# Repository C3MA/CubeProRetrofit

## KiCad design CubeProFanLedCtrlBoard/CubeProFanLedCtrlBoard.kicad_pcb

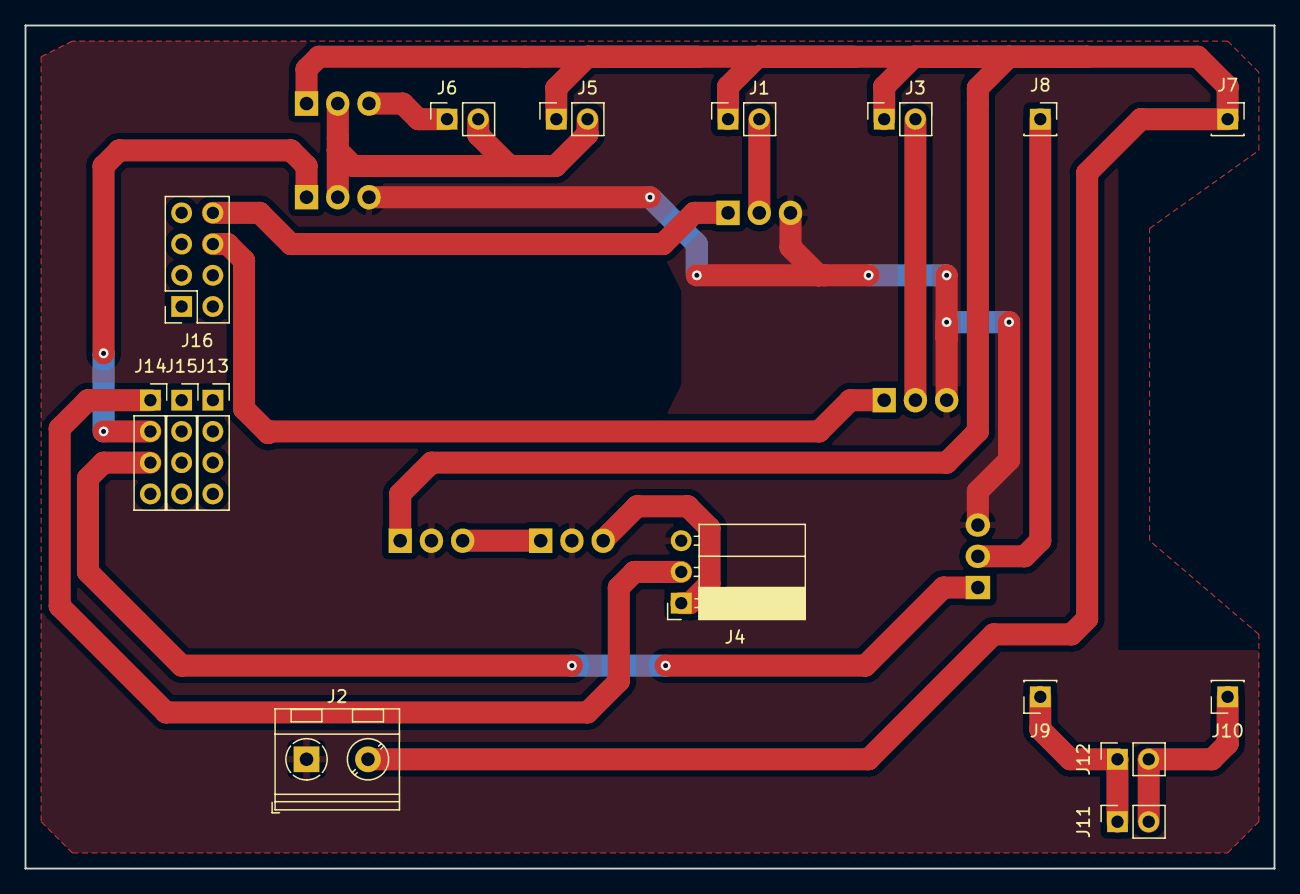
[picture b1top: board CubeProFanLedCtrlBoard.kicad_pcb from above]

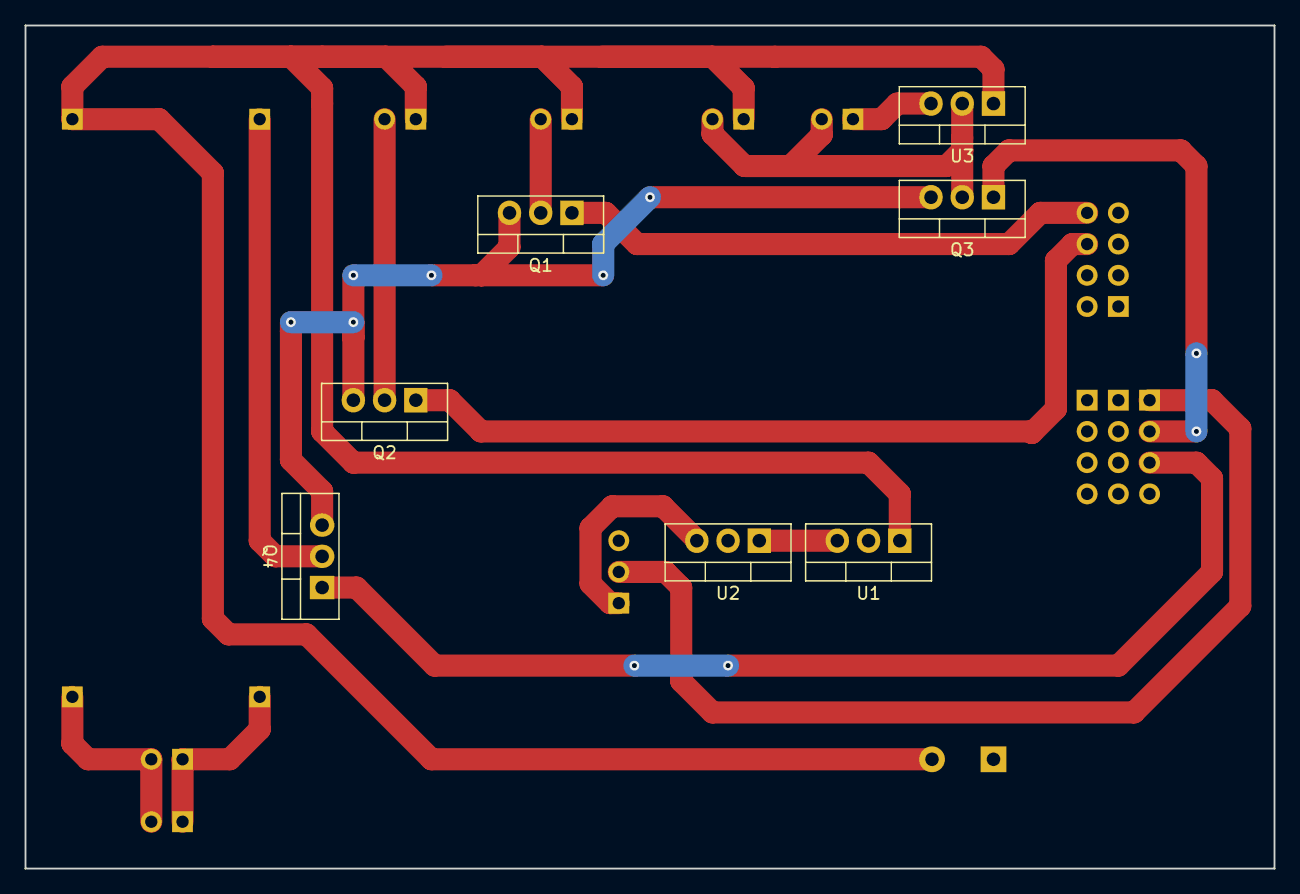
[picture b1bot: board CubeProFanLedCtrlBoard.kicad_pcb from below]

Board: 2 copper layers, 101.6 x 68.6 mm, 23 parts (7 on the bottom side), 16 nets.

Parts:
J1, J3, J5, J6, J11, J12: Conn_01x02; PinSocket_1x02_P2.54mm_Vertical
J2: Screw_Terminal_01x02; TerminalBlock_RND_205-00045_1x02_P5.00mm_Horizontal
J4: Conn_01x03; PinSocket_1x03_P2.54mm_Horizontal
J7, J8, J9, J10: Conn_01x01; PinSocket_1x01_P2.54mm_Vertical
J13, J14, J15: Conn_01x04; PinSocket_1x04_P2.54mm_Vertical
J16: Conn_02x04_Top_Bottom; PinSocket_2x04_P2.54mm_Vertical
Q1, Q2, Q3, Q4: IRF540N; TO-220-3_Vertical
U1, U3: L7812; TO-220-3_Vertical
U2: L7805; TO-220-3_Vertical

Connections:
+24V: J1.1, J2.2, J3.1, J5.1, J7.1, U1.1, U3.1
CaseFan: J14.2, Q3.1
CaseLEDs: J14.3, Q4.1
GND: J2.1, J4.3, Q1.3, Q2.3, Q3.3, Q4.3, U1.2, U2.2
HotBedFan: J16.6, Q2.1
HotEndFan: J16.8, Q1.1
unnamed: J1.2, Q1.2
unnamed: J3.2, Q2.2
unnamed: J4.1, U2.3
unnamed: J5.2, J6.2, Q3.2, U3.2
unnamed: J6.1, U3.3
unnamed: J8.1, Q4.2
unnamed: J10.1, J11.2, J12.2
unnamed: J9.1, J11.1, J12.1
unnamed: U1.3, U2.1
WS2812Led: J4.2, J14.1

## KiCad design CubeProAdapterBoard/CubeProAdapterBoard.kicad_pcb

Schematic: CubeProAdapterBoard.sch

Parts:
J1: X1(B); Molex_KK-254_AE-6410-04A_1x04_P2.54mm_Vertical
J2: FAN2 Hot End; Molex_KK-254_AE-6410-02A_1x02_P2.54mm_Vertical
J3: E2; Molex_KK-254_AE-6410-04A_1x04_P2.54mm_Vertical
J4: FAN1 Hot End; Molex_KK-254_AE-6410-02A_1x02_P2.54mm_Vertical
J5: X2(B); Molex_KK-254_AE-6410-04A_1x04_P2.54mm_Vertical
J6: E1; Molex_KK-254_AE-6410-04A_1x04_P2.54mm_Vertical
J7: Printer FAN; Molex_KK-254_AE-6410-06A_1x06_P2.54mm_Vertical
J8: Conn_01x10_Male; Molex_KK-254_AE-6410-10A_1x10_P2.54mm_Vertical
J9: LED; Molex_KK-254_AE-6410-02A_1x02_P2.54mm_Vertical
U1: L7812; Converter_DCDC_RECOM_R-78HB-0.5_THT

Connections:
E1Temp1: J6.2, J8.6
E1Temp2: J6.3, J8.7
E2Temp1: J3.2, J8.2
E2Temp2: J3.3, J8.3
FAN_24V: J7.4, J8.4, U1.1 (IN)
FAN_GND: J7.1, J7.5, J8.5, U1.2 (GND)
GND: J2.2, J8.10, J9.2
unnamed: J1.1, J1.2, J3.1
unnamed: J1.3, J1.4, J3.4
unnamed: J2.1, J4.2
unnamed: J4.1, J8.9
unnamed: J5.1, J5.2, J6.1
unnamed: J5.3, J5.4, J6.4
unnamed: J7.2, J7.3
unnamed: J7.6, U1.3 (OUT)
unnamed: J8.1, J9.1

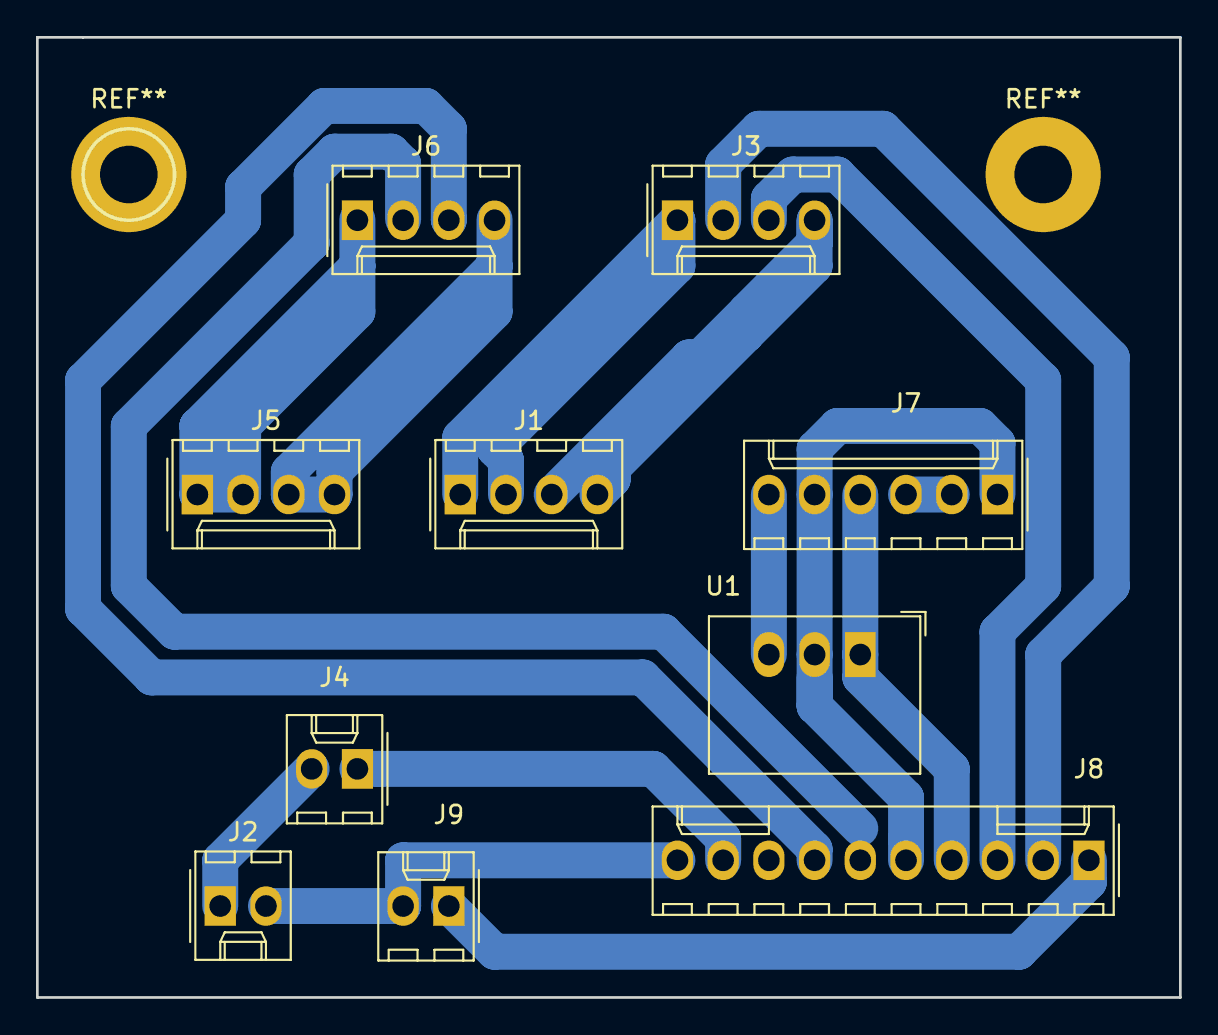
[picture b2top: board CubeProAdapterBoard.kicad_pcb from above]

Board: 2 copper layers, 63.5 x 53.3 mm, 10 parts (0 on the bottom side), 16 nets.

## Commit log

2018-05-21 First version
2018-05-21 Add the KiCad project itself
2018-06-01 Fan and LED Control Board
2018-06-03 Moved A3 and A4 to correct pin
2018-06-08 Moved HotEndFan and HotBedFan
2018-06-08 Added additional files
2018-06-27 Updated board
2018-06-27 Exported schema
2018-09-05 Marlin 1.1.9 201800829-Acid
2018-10-31 Swapped X and Y axis on board; improved homing
